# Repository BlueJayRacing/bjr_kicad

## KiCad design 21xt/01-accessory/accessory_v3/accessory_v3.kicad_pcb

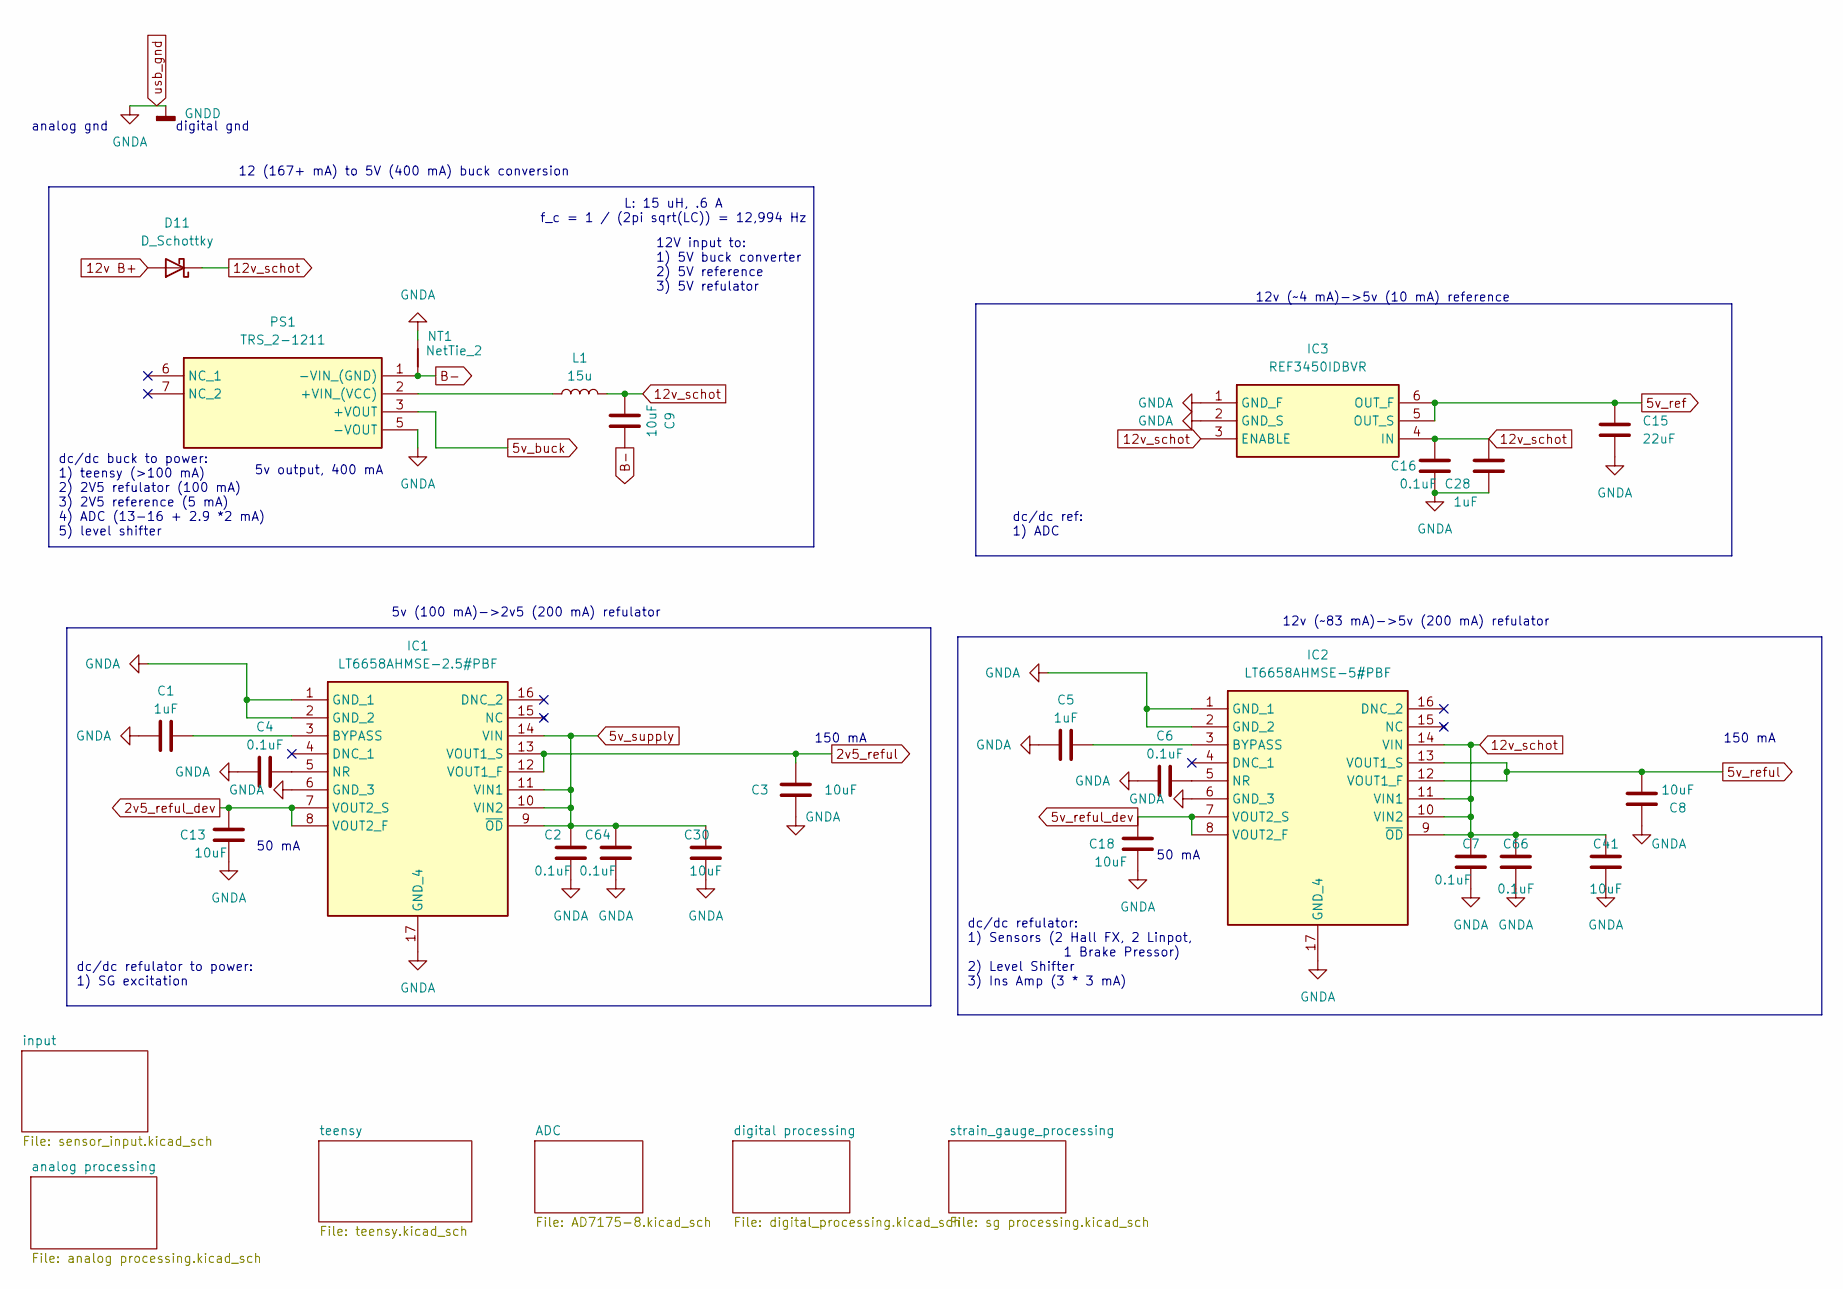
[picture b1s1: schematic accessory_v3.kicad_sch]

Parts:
C1, C5, C28: 1uF; C_0402_1005Metric
C2, C4, C6, C7, C16, C64, C66: 0.1uF; C_0402_1005Metric
C3, C8, C9, C13, C18, C30, C41: 10uF; C_0603_1608Metric
C15: 22uF; C_0603_1608Metric
D11: D_Schottky; D_1206_3216Metric
IC1: LT6658AHMSE-2.5#PBF; SOP50P490X110-17N; Mouser Part Number 584-LT6658AHMSE5PBF
IC2: LT6658AHMSE-5#PBF; SOP50P490X110-17N; Mouser Part Number 584-LT6658AHMSE5PBF
IC3: REF3450IDBVR; Mouser Part Number 595-REF3450IDBVR
L1: 15u; IND_TCK-147_TRP
NT1: NetTie_2; NetTie-2_SMD_Pad0.5mm
PS1: TRS_2-1211; CONV_TRS_2-2419; Mouser Part Number 495-TRS2-1211

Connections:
2v5_reful: C3.2, IC1.12 (VOUT1_F), IC1.13 (VOUT1_S); also elsewhere on the board
2v5_reful_dev: C13.2, IC1.7 (VOUT2_S), IC1.8 (VOUT2_F)
5v_buck: PS1.3 (+VOUT); also elsewhere on the board
5v_ref: C15.1, IC3.5 (OUT_S), IC3.6 (OUT_F); also elsewhere on the board
5v_reful: C8.2, IC2.12 (VOUT1_F), IC2.13 (VOUT1_S); also elsewhere on the board
5v_reful_dev: C18.2, IC2.7 (VOUT2_S), IC2.8 (VOUT2_F); also elsewhere on the board
5v_supply: C2.2, C30.2, C64.2, IC1.9 (~OD), IC1.10 (VIN2), IC1.11 (VIN1), IC1.14 (VIN); also elsewhere on the board
12v B+: D11.2 (A); also elsewhere on the board
12v_schot: C7.2, C9.1, C16.1, C28.1, C41.2, C66.2, D11.1 (K), IC2.9 (~OD), IC2.10 (VIN2), IC2.11 (VIN1), IC2.14 (VIN), IC3.3 (ENABLE), IC3.4 (IN), L1.2
B-: C9.2, NT1.1, PS1.1 (-VIN_(GND)); also elsewhere on the board
unnamed: C1.2, IC1.3 (BYPASS)
unnamed: C4.2, IC1.5 (NR)
unnamed: C5.2, IC2.3 (BYPASS)
unnamed: C6.2, IC2.5 (NR)
unnamed: L1.1, PS1.2 (+VIN_(VCC))
usb_gnd: C1.1, C2.1, C3.1, C4.1, C5.1, C6.1, C7.1, C8.1, C13.1, C15.2, C16.2, C18.1, C28.2, C30.1, C41.1, C64.1, C66.1, IC1.1 (GND_1), IC1.2 (GND_2), IC1.6 (GND_3), IC1.17 (GND_4), IC2.1 (GND_1), IC2.2 (GND_2), IC2.6 (GND_3), IC2.17 (GND_4), IC3.1 (GND_F), IC3.2 (GND_S), NT1.2, PS1.5 (-VOUT); also elsewhere on the board

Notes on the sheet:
dc/dc refulator to power: 1) SG excitation
150 mA
50 mA
analog gnd
dc/dc ref: 1) ADC
12 (167+ mA) to 5V (400 mA) buck conversion
L: 15 uH, .6 A f_c = 1 / (2pi sqrt(LC)) = 12,994 Hz
12V input to: 1) 5V buck converter 2) 5V reference 3) 5V refulator
5v (100 mA)->2v5 (200 mA) refulator
12v (~83 mA)->5v (200 mA) refulator
digital gnd
dc/dc refulator: 1) Sensors (2 Hall FX, 2 Linpot, 1 Brake Pressor) 2) Level Shifter 3) Ins Amp (3 * 3 mA)
dc/dc buck to power: 1) teensy (>100 mA) 2) 2V5 refulator (100 mA) 3) 2V5 reference (5 mA) 4) ADC (13-16 + 2.9 *2 mA) 5) level shifter
5v output, 400 mA
150 mA
12v (~4 mA)->5v (10 mA) reference

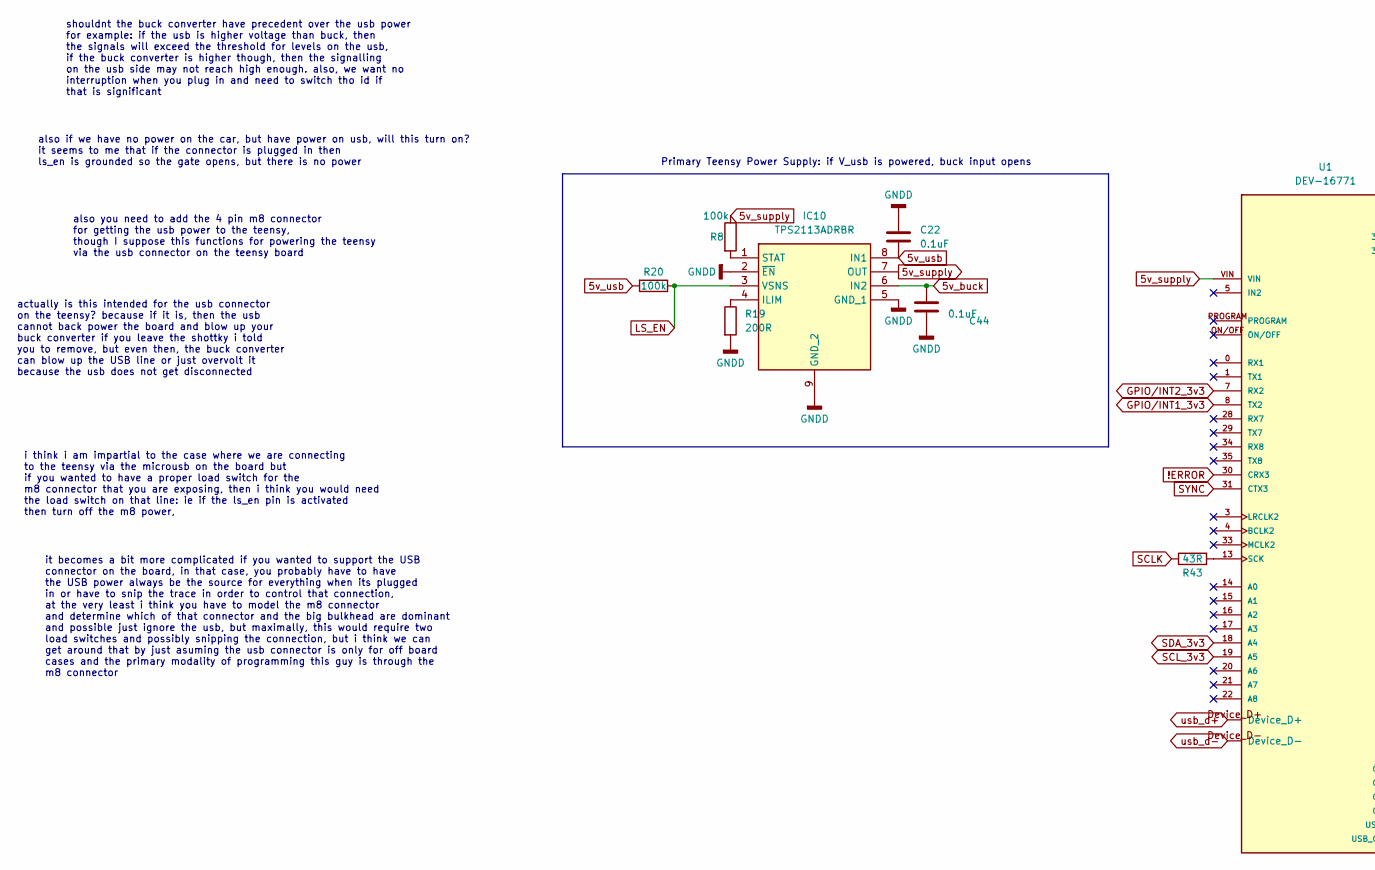
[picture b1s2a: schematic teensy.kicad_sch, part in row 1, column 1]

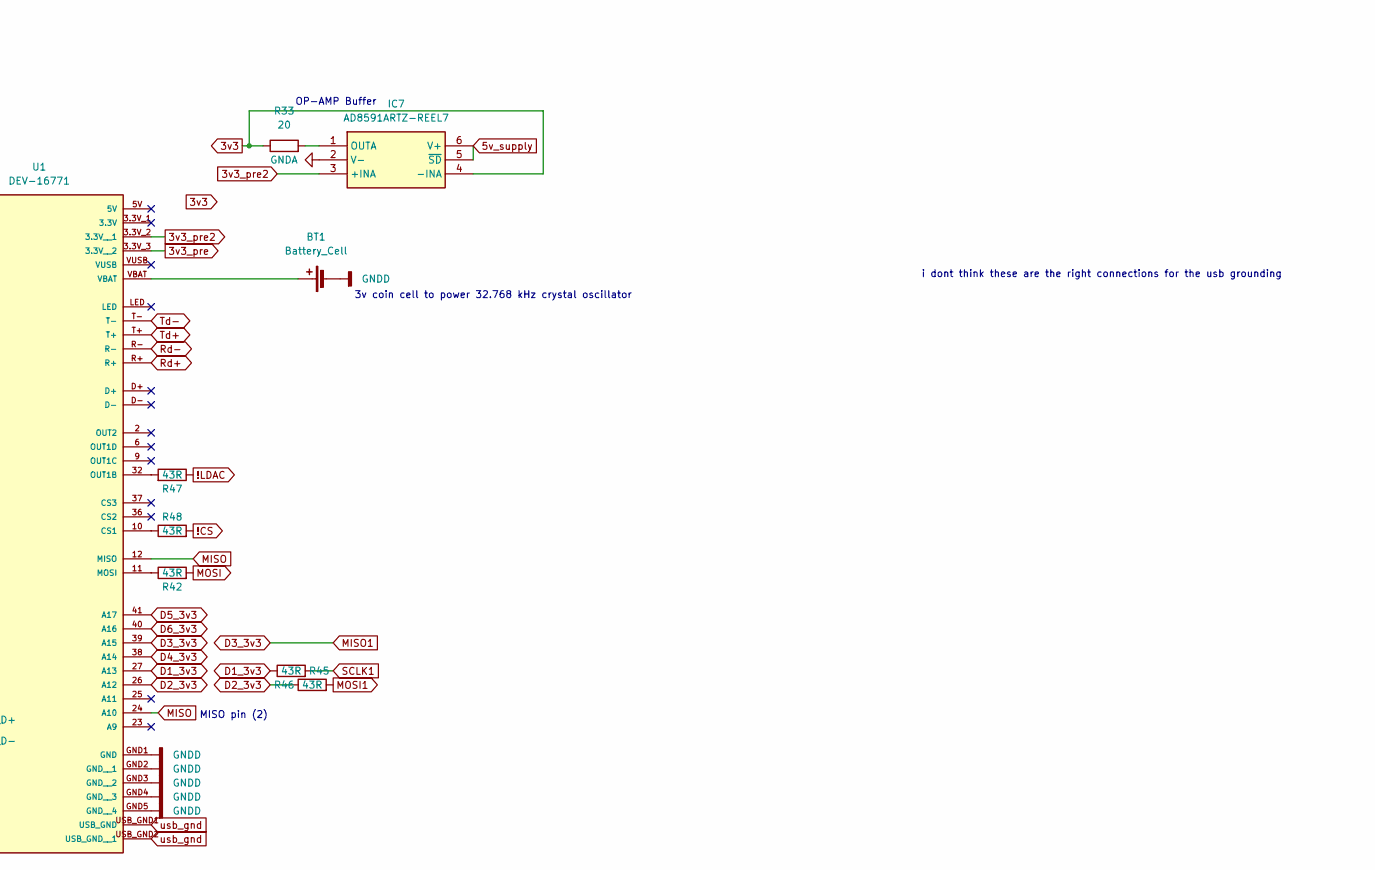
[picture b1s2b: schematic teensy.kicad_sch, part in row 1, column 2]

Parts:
BT1: Battery_Cell; 1220 holder
C22, C44: 0.1uF; C_0402_1005Metric
IC7: AD8591ARTZ-REEL7; SOT95P280X145-6N; Mouser Part Number 584-AD8591ARTZ-R7
IC10: TPS2113ADRBR; Mouser Part Number 595-TPS2113ADRBR
R8, R20: 100k; R_0402_1005Metric
R19: 200R; R_0402_1005Metric
R33: 20; R_0402_1005Metric
R42, R43, R45, R46, R47, R48: 43R; R_0402_1005Metric
U1: DEV-16771; MODULE_DEV-16771; PARTREV 4.1

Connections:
3v3: IC7.4 (-INA), R33.1; also elsewhere on the board
3v3_pre2: IC7.3 (+INA), U1.3.3V_2 (3.3V__1); also elsewhere on the board
5v_buck: C44.1, IC10.6 (IN2); also elsewhere on the board
5v_supply: IC7.5 (~SD), IC7.6 (V+), IC10.7 (OUT), R8.1, U1.VIN; also elsewhere on the board
5v_usb: C22.2, IC10.8 (IN1), R20.2; also elsewhere on the board
!CS: R48.2; also elsewhere on the board
!ERROR: U1.30 (CRX3); also elsewhere on the board
!LDAC: R47.1; also elsewhere on the board
D1_3v3: R45.1, U1.27 (A13); also elsewhere on the board
D2_3v3: R46.1, U1.26 (A12); also elsewhere on the board
D3_3v3: U1.39 (A15); also elsewhere on the board
D4_3v3: U1.38 (A14); also elsewhere on the board
D5_3v3: U1.41 (A17); also elsewhere on the board
D6_3v3: U1.40 (A16); also elsewhere on the board
GPIO/INT1_3v3: U1.8 (TX2); also elsewhere on the board
GPIO/INT2_3v3: U1.7 (RX2); also elsewhere on the board
LS_EN: IC10.3 (VSNS), R20.1; also elsewhere on the board
MISO: U1.12 (MISO), U1.24 (A10); also elsewhere on the board
MOSI: R42.2; also elsewhere on the board
MOSI1: R46.2; also elsewhere on the board
unnamed: BT1.1 (+), U1.VBAT
unnamed: IC7.1 (OUTA), R33.2
unnamed: IC10.4 (ILIM), R19.1
unnamed: IC10.1 (STAT), R8.2
unnamed: R48.1, U1.10 (CS1)
unnamed: R42.1, U1.11 (MOSI)
unnamed: R47.2, U1.32 (OUT1B)
unnamed: R43.2, U1.13 (SCK)
Rd+: U1.R+; also elsewhere on the board
Rd-: U1.R-; also elsewhere on the board
SCLK: R43.1; also elsewhere on the board
SCLK1: R45.2; also elsewhere on the board
SCL_3v3: U1.19 (A5); also elsewhere on the board
SDA_3v3: U1.18 (A4); also elsewhere on the board
SYNC: U1.31 (CTX3); also elsewhere on the board
Td+: U1.T+; also elsewhere on the board
Td-: U1.T-; also elsewhere on the board
usb_d+: U1.Device_D+; also elsewhere on the board
usb_d-: U1.Device_D-; also elsewhere on the board
usb_gnd: BT1.2 (-), C22.1, C44.2, IC7.2 (V-), IC10.2 (~EN), IC10.5 (GND_1), IC10.9 (GND_2), R19.2, U1.GND1 (GND), U1.GND2 (GND__1), U1.GND3 (GND__2), U1.GND4 (GND__3), U1.GND5 (GND__4), U1.USB_GND1 (USB_GND), U1.USB_GND2 (USB_GND__1); also elsewhere on the board

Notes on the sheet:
Primary Teensy Power Supply: if V_usb is powered, buck input opens
3v coin cell to power 32.768 kHz crystal oscillator
it becomes a bit more complicated if you wanted to support the USB connector on the board, in that case, you probably have to have the USB power always be the source for everything when its plugged in or have to snip the trace in order to control that connection, at the very least i think you have 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
shouldnt the buck converter have precedent over the usb power for example: if the usb is higher voltage than buck, then the signals will exceed the threshold for levels on the usb, if the buck converter is higher though, then the signalling on the usb side may not reach high enough. also, we want n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
actually is this intended for the usb connector on the teensy? because if it is, then the usb cannot back power the board and blow up your buck converter if you leave the shottky i told you to remove, but even then, the buck converter can blow up the USB line or just overvolt it because the usb doe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
MISO pin (2)
also you need to add the 4 pin m8 connector for getting the usb power to the teensy, though I suppose this functions for powering the teensy via the usb connector on the teensy board
i think i am impartial to the case where we are connecting to the teensy via the microusb on the board but if you wanted to have a proper load switch for the m8 connector that you are exposing, then i think you would need the load switch on that line: ie if the ls_en pin is activated then turn off 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
i dont think these are the right connections for the usb grounding
also if we have no power on the car, but have power on usb, will this turn on? it seems to me that if the connector is plugged in then ls_en is grounded so the gate opens, but there is no power
OP-AMP Buffer

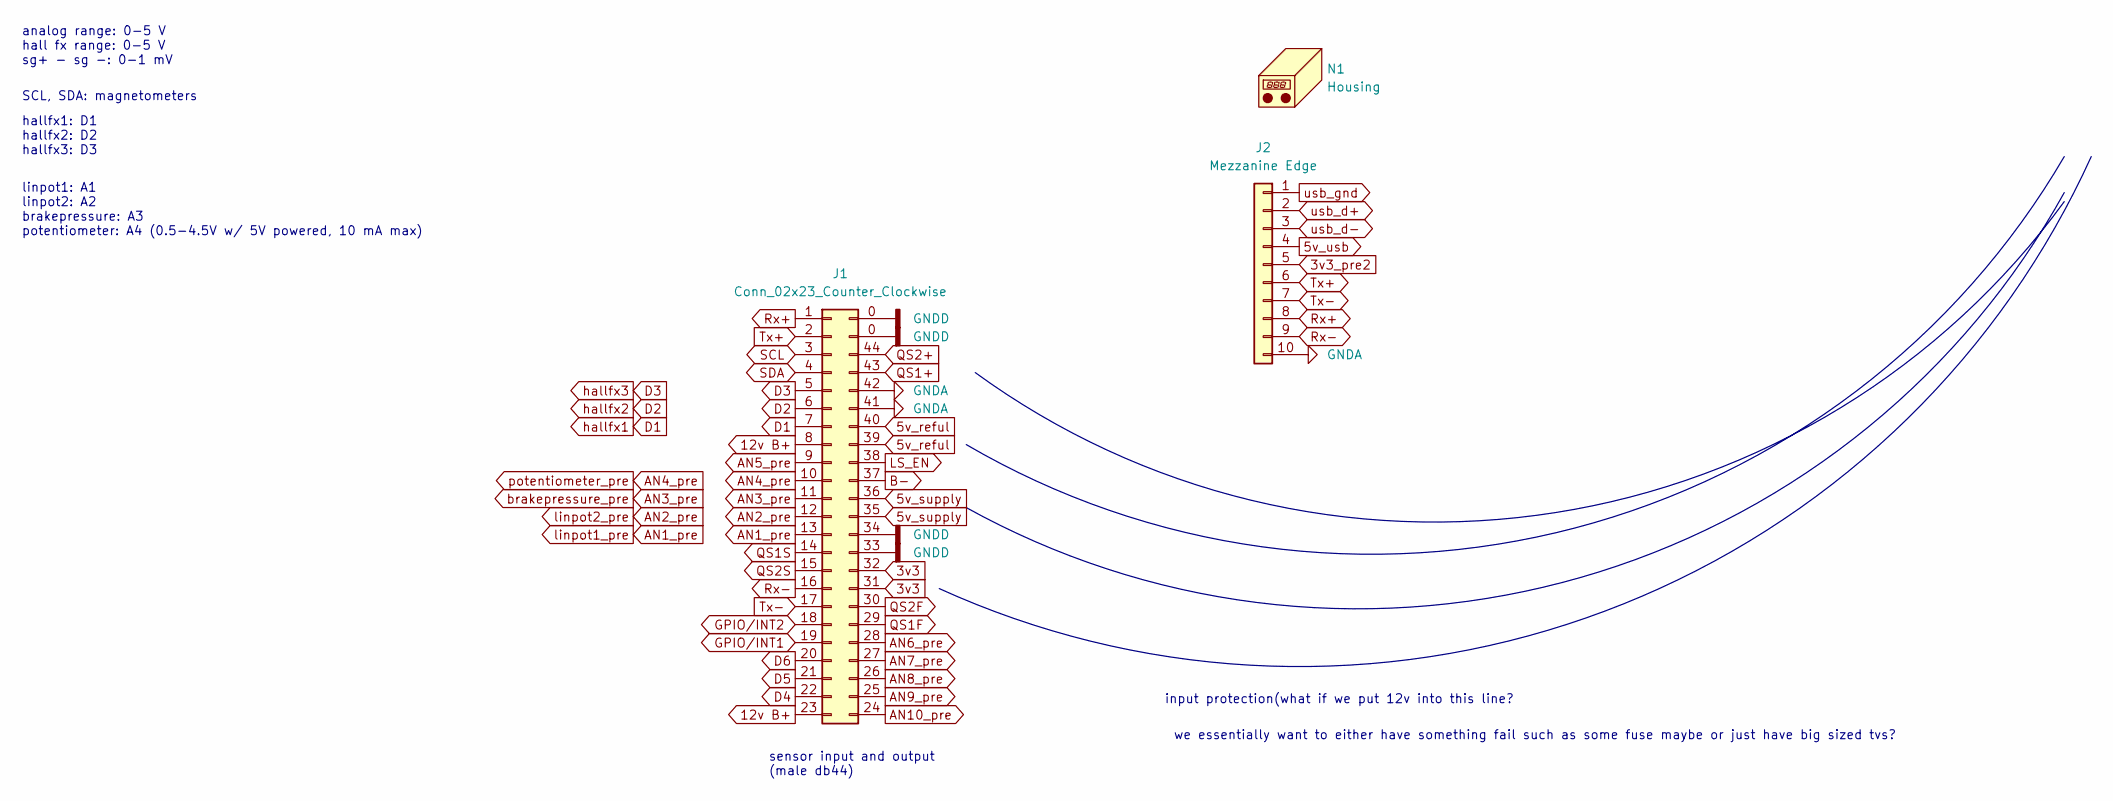
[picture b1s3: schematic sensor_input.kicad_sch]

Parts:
J1: Conn_02x23_Counter_Clockwise; aaren_mouser_db44_screws
J2: Mezzanine Edge; Double Sided Mezzanine Card Edge_Edge Side
N1: Housing

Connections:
2v5_reful: J1.43, J1.44; also elsewhere on the board
3v3: J1.31, J1.32; also elsewhere on the board
3v3_pre2: J2.5; also elsewhere on the board
5v_reful: J1.39, J1.40; also elsewhere on the board
5v_supply: J1.35, J1.36; also elsewhere on the board
5v_usb: J2.4; also elsewhere on the board
12v B+: J1.8, J1.23; also elsewhere on the board
AN1_pre: J1.13; also elsewhere on the board
AN2_pre: J1.12; also elsewhere on the board
AN3_pre: J1.11; also elsewhere on the board
AN4_pre: J1.10; also elsewhere on the board
AN5_pre: J1.9; also elsewhere on the board
AN6_pre: J1.28; also elsewhere on the board
AN7_pre: J1.27; also elsewhere on the board
AN8_pre: J1.26; also elsewhere on the board
AN9_pre: J1.25; also elsewhere on the board
AN10_pre: J1.24; also elsewhere on the board
B-: J1.37; also elsewhere on the board
D1: J1.7; also elsewhere on the board
D2: J1.6; also elsewhere on the board
D3: J1.5; also elsewhere on the board
D4: J1.22; also elsewhere on the board
D5: J1.21; also elsewhere on the board
D6: J1.20; also elsewhere on the board
GPIO/INT1: J1.19; also elsewhere on the board
GPIO/INT2: J1.18; also elsewhere on the board
LS_EN: J1.38; also elsewhere on the board
QS1F: J1.29; also elsewhere on the board
QS1S: J1.14; also elsewhere on the board
QS2F: J1.30; also elsewhere on the board
QS2S: J1.15; also elsewhere on the board
Rx+: J1.1, J2.8; also elsewhere on the board
Rx-: J1.16, J2.9; also elsewhere on the board
SCL: J1.3; also elsewhere on the board
SDA: J1.4; also elsewhere on the board
Tx+: J1.2, J2.6; also elsewhere on the board
Tx-: J1.17, J2.7; also elsewhere on the board
usb_d+: J2.2; also elsewhere on the board
usb_d-: J2.3; also elsewhere on the board
usb_gnd: J1.0 (Pin_45), J1.33, J1.34, J1.41, J1.42, J2.1, J2.10; also elsewhere on the board

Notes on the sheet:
SCL, SDA: magnetometers
sensor input and output (male db44)
analog range: 0-5 V hall fx range: 0-5 V sg+ - sg -: 0-1 mV
linpot1: A1 linpot2: A2 brakepressure: A3 potentiometer: A4 (0.5-4.5V w/ 5V powered, 10 mA max)
we essentially want to either have something fail such as some fuse maybe or just have big sized tvs?
hallfx1: D1 hallfx2: D2 hallfx3: D3
input protection(what if we put 12v into this line?

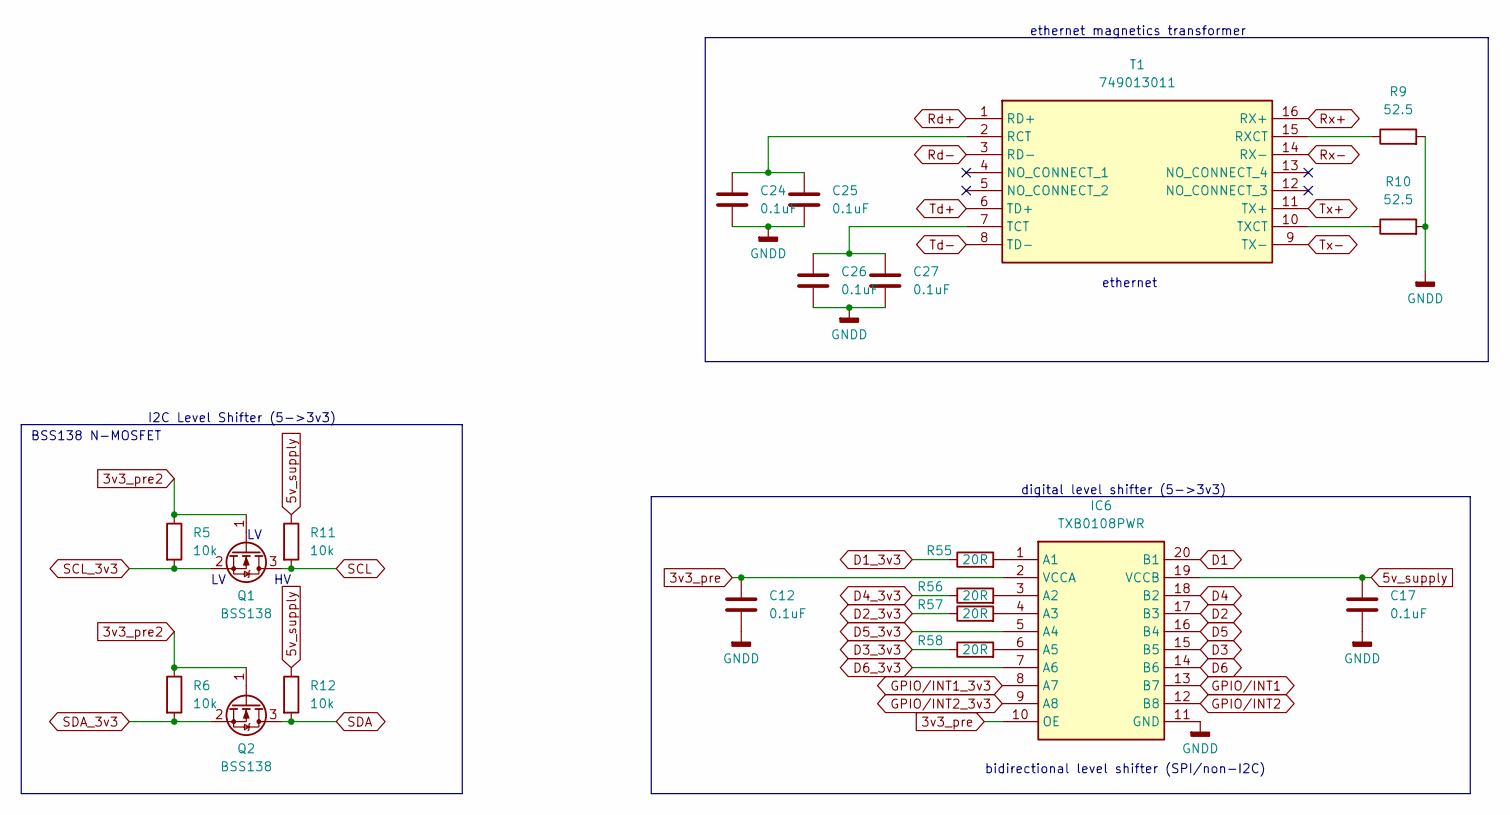
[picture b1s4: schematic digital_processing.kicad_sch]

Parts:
C12, C17, C24, C25, C26, C27: 0.1uF; C_0402_1005Metric
IC6: TXB0108PWR; SOP65P640X120-20N; Mouser Part Number 595-TXB0108PWR
Q1, Q2: BSS138; SOT-23
R5, R6, R11, R12: 10k; R_0402_1005Metric
R9, R10: 52.5; R_0402_1005Metric
R55, R56, R57, R58: 20R; R_0402_1005Metric
T1: 749013011; Mouser Part Number 710-749013011

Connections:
3v3_pre2: Q1.1 (G), Q2.1 (G), R5.1, R6.1; also elsewhere on the board
5v_supply: C17.1, IC6.19 (VCCB), R11.1, R12.1; also elsewhere on the board
D1: IC6.20 (B1); also elsewhere on the board
D1_3v3: R55.1; also elsewhere on the board
D2: IC6.17 (B3); also elsewhere on the board
D2_3v3: R57.1; also elsewhere on the board
D3: IC6.15 (B5); also elsewhere on the board
D3_3v3: R58.1; also elsewhere on the board
D4: IC6.18 (B2); also elsewhere on the board
D4_3v3: R56.1; also elsewhere on the board
D5: IC6.16 (B4); also elsewhere on the board
D5_3v3: IC6.5 (A4); also elsewhere on the board
D6: IC6.14 (B6); also elsewhere on the board
D6_3v3: IC6.7 (A6); also elsewhere on the board
GPIO/INT1: IC6.13 (B7); also elsewhere on the board
GPIO/INT1_3v3: IC6.8 (A7); also elsewhere on the board
GPIO/INT2: IC6.12 (B8); also elsewhere on the board
GPIO/INT2_3v3: IC6.9 (A8); also elsewhere on the board
unnamed: IC6.1 (A1), R55.2
unnamed: IC6.3 (A2), R56.2
unnamed: IC6.4 (A3), R57.2
unnamed: IC6.6 (A5), R58.2
unnamed: C24.1, C25.1, T1.2 (RCT)
unnamed: R9.1, T1.15 (RXCT)
unnamed: C26.1, C27.1, T1.7 (TCT)
unnamed: R10.1, T1.10 (TXCT)
Rd+: T1.1 (RD+); also elsewhere on the board
Rd-: T1.3 (RD-); also elsewhere on the board
Rx+: T1.16 (RX+); also elsewhere on the board
Rx-: T1.14 (RX-); also elsewhere on the board
SCL: Q1.3 (D), R11.2; also elsewhere on the board
SCL_3v3: Q1.2 (S), R5.2; also elsewhere on the board
SDA: Q2.3 (D), R12.2; also elsewhere on the board
SDA_3v3: Q2.2 (S), R6.2; also elsewhere on the board
Td+: T1.6 (TD+); also elsewhere on the board
Td-: T1.8 (TD-); also elsewhere on the board
Tx+: T1.11 (TX+); also elsewhere on the board
Tx-: T1.9 (TX-); also elsewhere on the board
usb_gnd: C12.2, C17.2, C24.2, C25.2, C26.2, C27.2, IC6.11 (GND), R9.2, R10.2; also elsewhere on the board

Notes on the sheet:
I2C Level Shifter (5->3v3)
ethernet magnetics transformer
digital level shifter (5->3v3)
bidirectional level shifter (SPI/non-I2C)
BSS138 N-MOSFET
ethernet

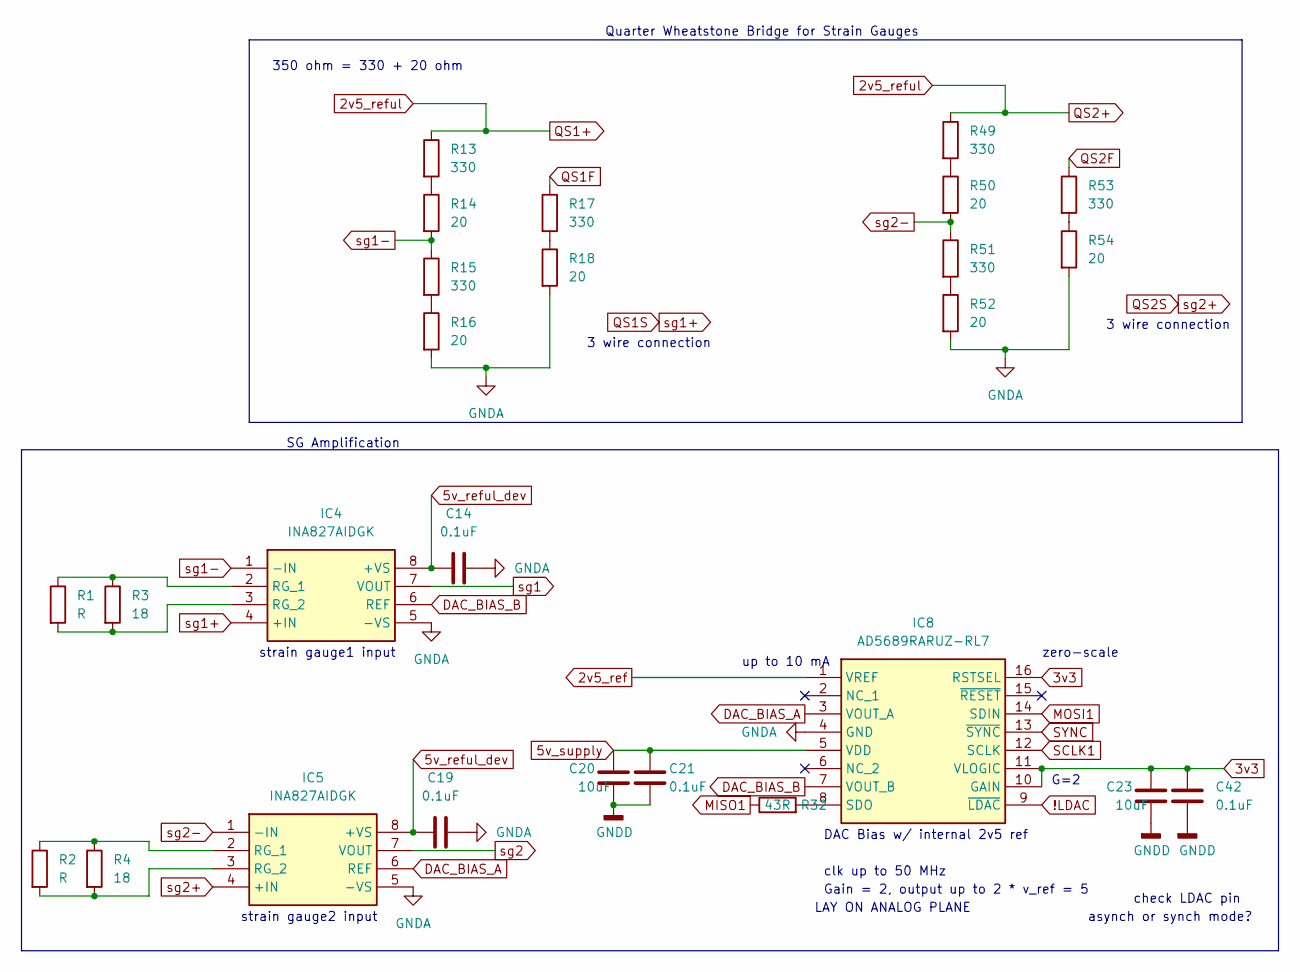
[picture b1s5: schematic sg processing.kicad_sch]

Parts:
C14, C19, C21, C42: 0.1uF; C_0402_1005Metric
C20, C23: 10uF; C_0603_1608Metric
IC4, IC5: INA827AIDGK; SOP65P490X110-8N; Mouser Part Number 595-INA827AIDGK
IC8: AD5689RARUZ-RL7; SOP65P640X120-16N; Mouser Part Number 584-AD5689RARUZ-R7
R1, R2: R; R_0402_1005Metric
R3, R4: 18; R_0402_1005Metric
R13, R15, R17, R49, R51, R53: 330; R_0402_1005Metric
R14, R16, R18, R50, R52, R54: 20; R_0402_1005Metric
R32: 43R; R_0402_1005Metric

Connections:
2v5_ref: IC8.1 (VREF); also elsewhere on the board
2v5_reful: R13.1, R49.1; also elsewhere on the board
5v_reful_dev: C14.1, C19.1, IC4.8 (+VS), IC5.8 (+VS); also elsewhere on the board
5v_supply: C20.1, C21.1, IC8.5 (VDD); also elsewhere on the board
!LDAC: IC8.9 (~LDAC); also elsewhere on the board
D3_3v3: R32.1; also elsewhere on the board
DAC_BIAS_A: IC5.6 (REF), IC8.3 (VOUT_A)
DAC_BIAS_B: IC4.6 (REF), IC8.7 (VOUT_B)
MOSI1: IC8.14 (SDIN); also elsewhere on the board
unnamed: IC4.2 (RG_1), R1.1, R3.1
unnamed: IC4.3 (RG_2), R1.2, R3.2
unnamed: IC5.2 (RG_1), R2.1, R4.1
unnamed: IC5.3 (RG_2), R2.2, R4.2
unnamed: IC8.8 (SDO), R32.2
unnamed: R13.2, R14.1
unnamed: R15.2, R16.1
unnamed: R17.2, R18.1
unnamed: R49.2, R50.1
unnamed: R51.2, R52.1
unnamed: R53.2, R54.1
QS1F: R17.1; also elsewhere on the board
QS1S: IC4.4 (+IN); also elsewhere on the board
QS2F: R53.1; also elsewhere on the board
QS2S: IC5.4 (+IN); also elsewhere on the board
SCLK1: IC8.12 (SCLK); also elsewhere on the board
SYNC: IC8.13 (~SYNC); also elsewhere on the board
sg1: IC4.7 (VOUT); also elsewhere on the board
sg1-: IC4.1 (-IN), R14.2, R15.1
sg2: IC5.7 (VOUT); also elsewhere on the board
sg2-: IC5.1 (-IN), R50.2, R51.1
usb_gnd: C14.2, C19.2, C20.2, C21.2, C23.2, C42.2, IC4.5 (-VS), IC5.5 (-VS), IC8.4 (GND), R16.2, R18.2, R52.2, R54.2; also elsewhere on the board

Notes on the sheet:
350 ohm = 330 + 20 ohm
clk up to 50 MHz
check LDAC pin
LAY ON ANALOG PLANE
Gain = 2, output up to 2 * v_ref = 5
SG Amplification
strain gauge2 input
zero-scale
asynch or synch mode?
up to 10 mA
Quarter Wheatstone Bridge for Strain Gauges
DAC Bias w/ internal 2v5 ref
G=2
strain gauge1 input
3 wire connection

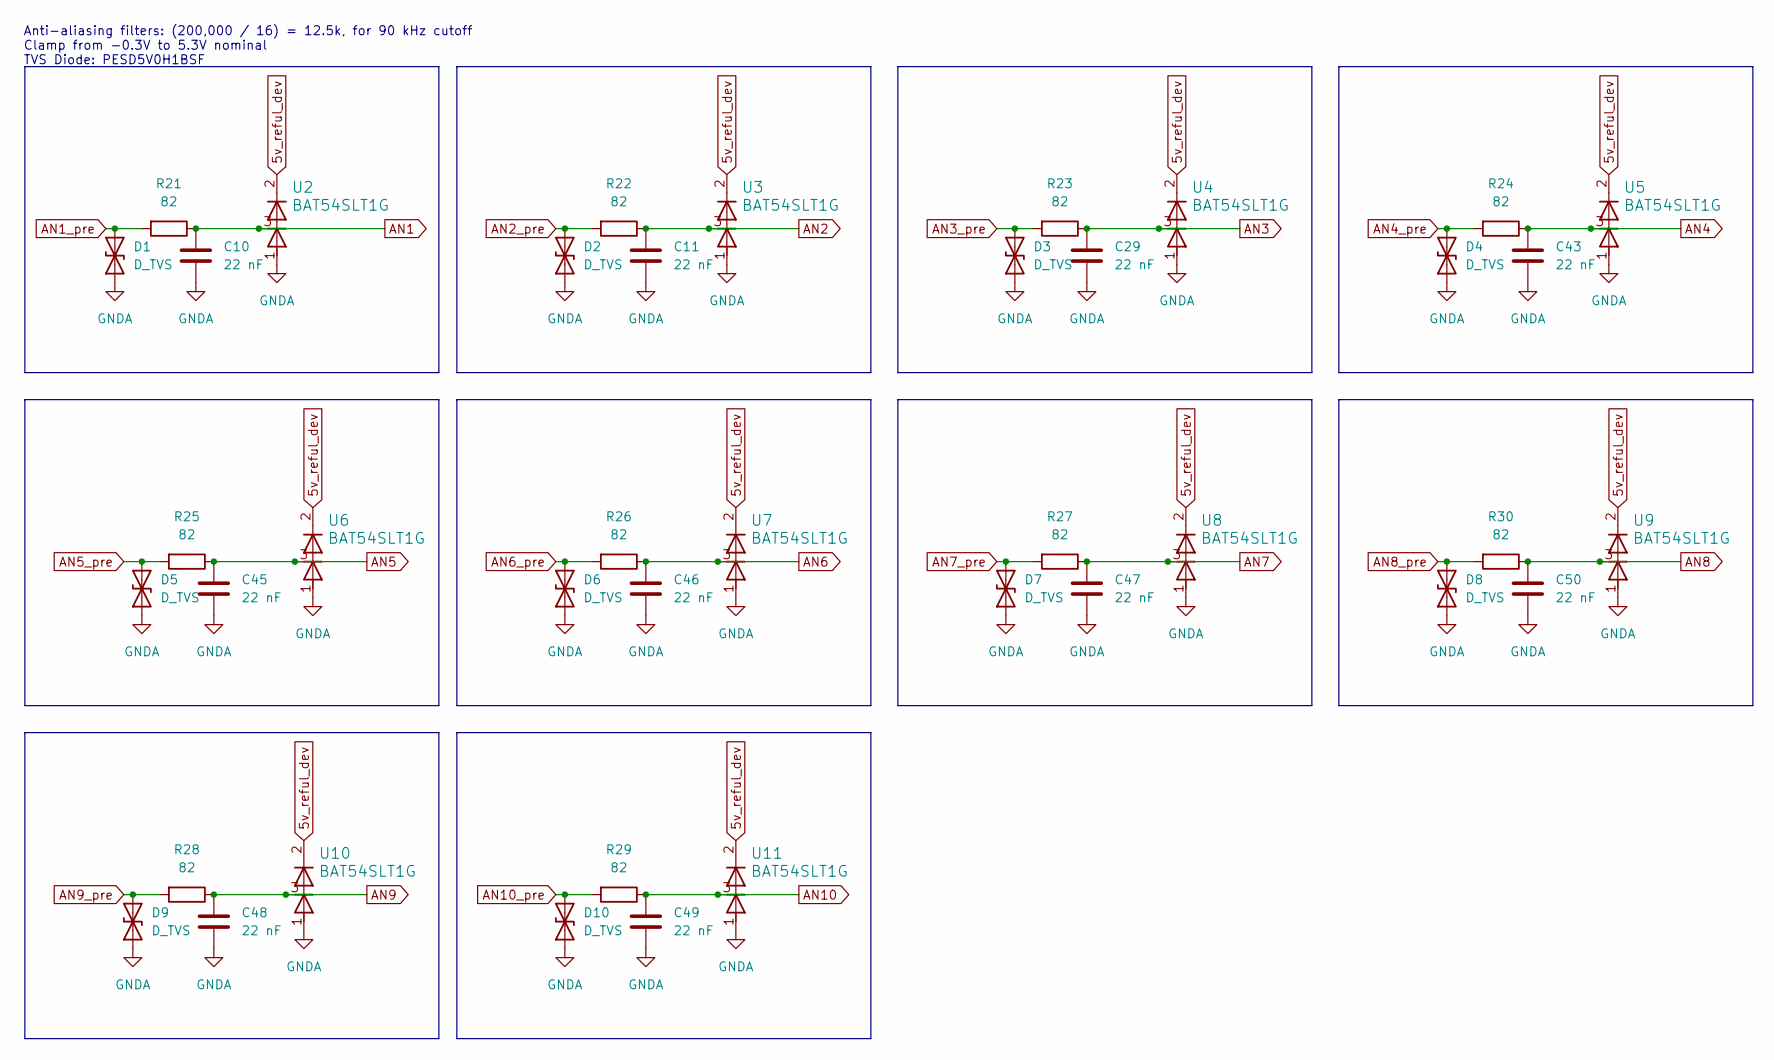
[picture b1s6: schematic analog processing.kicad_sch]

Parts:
C10, C11, C29, C43, C45, C46, C47, C48, C49, C50: 22 nF; C_0402_1005Metric
D1, D2, D3, D4, D5, D6, D7, D8, D9, D10: D_TVS; PESD5V0H1BSFYL_NEX
R21, R22, R23, R24, R25, R26, R27, R28, R29, R30: 82; R_0402_1005Metric
U2, U3, U4, U5, U6, U7, U8, U9, U10, U11: BAT54SLT1G; SOT-723 VESM_TOS

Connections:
5v_reful_dev: U2.2, U3.2, U4.2, U5.2, U6.2, U7.2, U8.2, U9.2, U10.2, U11.2; also elsewhere on the board
AN1: C10.1, R21.1, U2.3; also elsewhere on the board
AN1_pre: D1.2 (A2), R21.2; also elsewhere on the board
AN2: C11.1, R22.1, U3.3; also elsewhere on the board
AN2_pre: D2.2 (A2), R22.2; also elsewhere on the board
AN3: C29.1, R23.1, U4.3; also elsewhere on the board
AN3_pre: D3.2 (A2), R23.2; also elsewhere on the board
AN4: C43.1, R24.1, U5.3; also elsewhere on the board
AN4_pre: D4.2 (A2), R24.2; also elsewhere on the board
AN5: C45.1, R25.1, U6.3; also elsewhere on the board
AN5_pre: D5.2 (A2), R25.2; also elsewhere on the board
AN6: C46.1, R26.1, U7.3; also elsewhere on the board
AN6_pre: D6.2 (A2), R26.2; also elsewhere on the board
AN7: C47.1, R27.1, U8.3; also elsewhere on the board
AN7_pre: D7.2 (A2), R27.2; also elsewhere on the board
AN8: C50.1, R30.1, U9.3; also elsewhere on the board
AN8_pre: D8.2 (A2), R30.2; also elsewhere on the board
AN9: C48.1, R28.1, U10.3; also elsewhere on the board
AN9_pre: D9.2 (A2), R28.2; also elsewhere on the board
AN10: C49.1, R29.1, U11.3; also elsewhere on the board
AN10_pre: D10.2 (A2), R29.2; also elsewhere on the board
usb_gnd: C10.2, C11.2, C29.2, C43.2, C45.2, C46.2, C47.2, C48.2, C49.2, C50.2, D1.1 (A1), D2.1 (A1), D3.1 (A1), D4.1 (A1), D5.1 (A1), D6.1 (A1), D7.1 (A1), D8.1 (A1), D9.1 (A1), D10.1 (A1), U2.1, U3.1, U4.1, U5.1, U6.1, U7.1, U8.1, U9.1, U10.1, U11.1; also elsewhere on the board

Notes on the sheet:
Anti-aliasing filters: (200,000 / 16) = 12.5k, for 90 kHz cutoff Clamp from -0.3V to 5.3V nominal TVS Diode: PESD5V0H1BSF

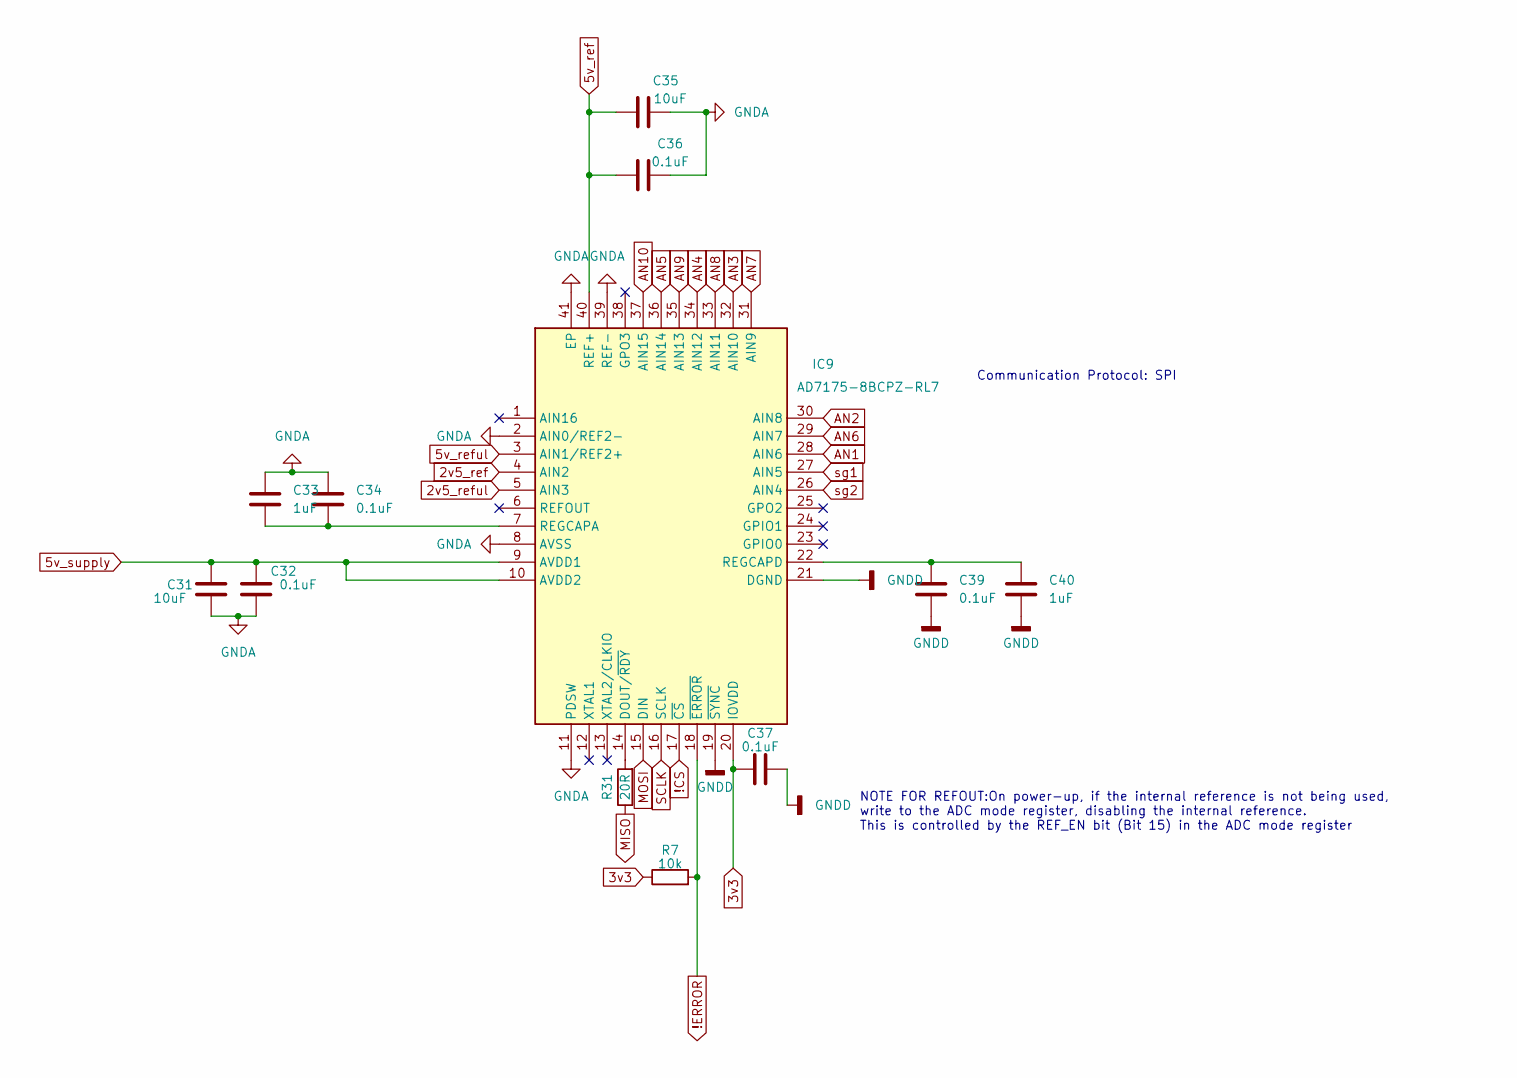
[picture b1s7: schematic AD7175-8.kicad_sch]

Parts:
C31, C35: 10uF; C_0603_1608Metric
C32, C34, C36, C37, C39: 0.1uF; C_0402_1005Metric
C33, C40: 1uF; C_0402_1005Metric
IC9: AD7175-8BCPZ-RL7; Mouser Part Number 584-AD7175-8BCPZ-RL7
R7: 10k; R_0402_1005Metric
R31: 20R; R_0402_1005Metric

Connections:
2v5_ref: IC9.4 (AIN2); also elsewhere on the board
2v5_reful: IC9.5 (AIN3); also elsewhere on the board
5v_ref: C35.1, C36.1, IC9.40 (REF+); also elsewhere on the board
5v_reful: IC9.3 (AIN1/REF2+); also elsewhere on the board
5v_supply: C31.1, C32.1, IC9.9 (AVDD1), IC9.10 (AVDD2); also elsewhere on the board
!CS: IC9.17 (~CS); also elsewhere on the board
!ERROR: IC9.18 (~ERROR), R7.2; also elsewhere on the board
AN1: IC9.28 (AIN6); also elsewhere on the board
AN2: IC9.30 (AIN8); also elsewhere on the board
AN3: IC9.32 (AIN10); also elsewhere on the board
AN4: IC9.34 (AIN12); also elsewhere on the board
AN5: IC9.36 (AIN14); also elsewhere on the board
AN6: IC9.29 (AIN7); also elsewhere on the board
AN7: IC9.31 (AIN9); also elsewhere on the board
AN8: IC9.33 (AIN11); also elsewhere on the board
AN9: IC9.35 (AIN13); also elsewhere on the board
AN10: IC9.37 (AIN15); also elsewhere on the board
MISO: R31.1; also elsewhere on the board
MOSI: IC9.15 (DIN); also elsewhere on the board
unnamed: IC9.14 (DOUT/~RDY), R31.2
unnamed: C33.2, C34.2, IC9.7 (REGCAPA)
unnamed: C39.1, C40.1, IC9.22 (REGCAPD)
SCLK: IC9.16 (SCLK); also elsewhere on the board
sg1: IC9.27 (AIN5); also elsewhere on the board
sg2: IC9.26 (AIN4); also elsewhere on the board
usb_gnd: C31.2, C32.2, C33.1, C34.1, C35.2, C36.2, C37.2, C39.2, C40.2, IC9.2 (AIN0/REF2-), IC9.8 (AVSS), IC9.11 (PDSW), IC9.19 (~SYNC), IC9.21 (DGND), IC9.39 (REF-), IC9.41 (EP); also elsewhere on the board

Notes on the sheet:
NOTE FOR REFOUT:On power-up, if the internal reference is not being used, write to the ADC mode register, disabling the internal reference. This is controlled by the REF_EN bit (Bit 15) in the ADC mode register
Communication Protocol: SPI

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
